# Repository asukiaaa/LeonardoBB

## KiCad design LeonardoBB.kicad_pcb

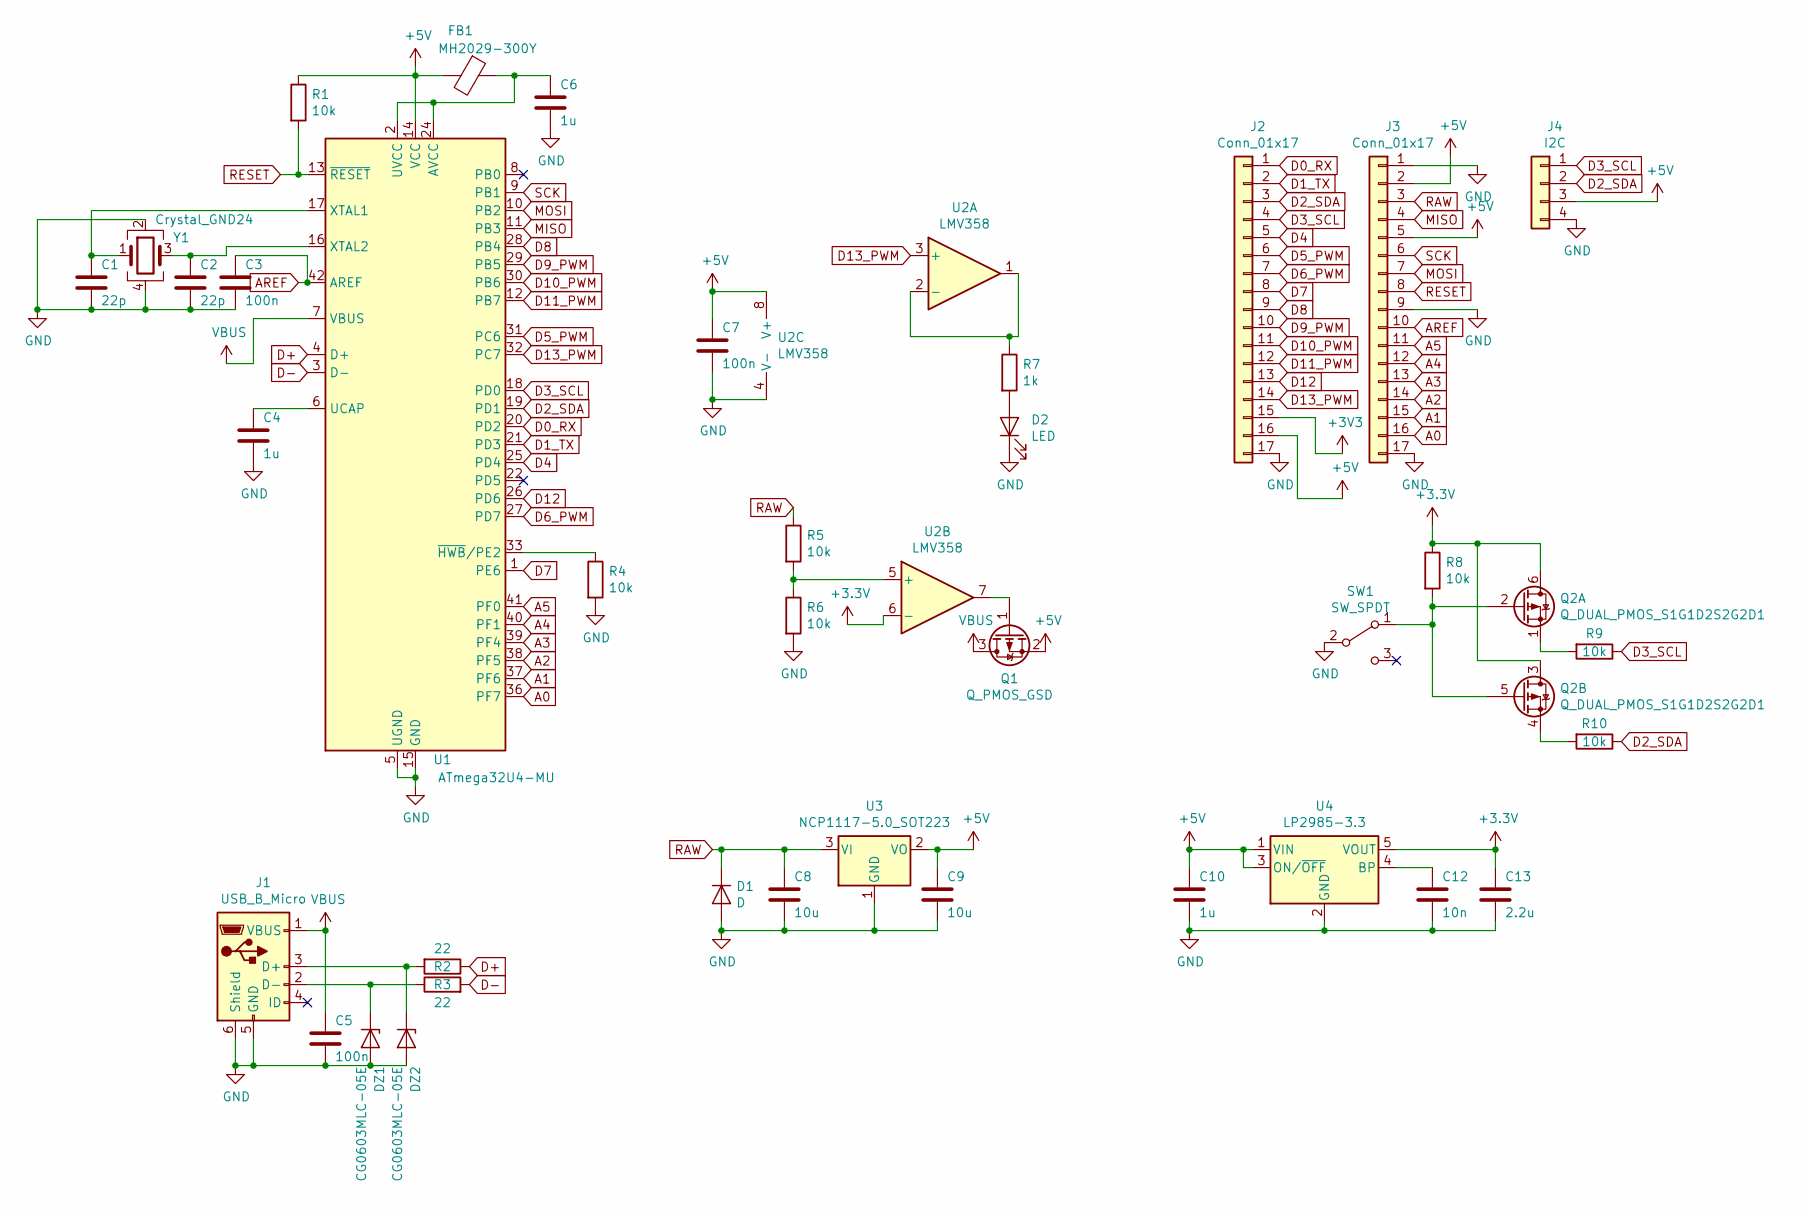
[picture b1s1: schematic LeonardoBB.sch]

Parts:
C1, C2: 22p; C_0402_1005Metric
C3, C5, C7: 100n; C_0402_1005Metric
C4, C6, C10: 1u; C_0402_1005Metric
C8, C9: 10u; C_0805_2012Metric
C12: 10n; C_0402_1005Metric
C13: 2.2u; C_0402_1005Metric
D1: D; D_SMA
D2: LED; LED_0603_1608Metric
DZ1, DZ2: CG0603MLC-05E; D_0603_1608Metric
FB1: MH2029-300Y; C_0805_2012Metric
J1: USB_B_Micro; USB_Micro-B_Molex-105017-0001
J2, J3: Conn_01x17; PinSocket_1x17_P2.54mm_Vertical_without_silk
J4: I2C; NS-Tech_Grove_1x04_P2mm_Vertical
Q1: Q_PMOS_GSD; SuperSOT-3
Q2: Q_DUAL_PMOS_S1G1D2S2G2D1; SOT-363_SC-70-6
R1, R4, R5, R6, R8, R9, R10: 10k; R_0603_1608Metric
R2, R3: 22; R_0603_1608Metric
R7: 1k; R_0603_1608Metric
SW1: SW_SPDT; SW_SPDT_PCM12
U1: ATmega32U4-MU; QFN-44-1EP_7x7mm_P0.5mm_EP5.2x5.2mm
U2: LMV358; VSSOP-8_3.0x3.0mm_P0.65mm
U3: NCP1117-5.0_SOT223; SOT-223-3_TabPin2
U4: LP2985-3.3; SOT-23-5
Y1: Crystal_GND24; Crystal_SMD_SeikoEpson_TSX3225-4Pin_3.2x2.5mm

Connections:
+5V: C7.1, C9.1, C10.1, FB1.2, J2.16, J3.2, J3.5, J4.3, Q1.2 (S), R1.1, U1.14 (VCC), U1.34 (VCC), U2.8 (V+), U3.2 (VO), U4.1 (VIN), U4.3 (ON/~OFF~)
A0: J3.16, U1.36 (PF7)
A1: J3.15, U1.37 (PF6)
A2: J3.14, U1.38 (PF5)
A3: J3.13, U1.39 (PF4)
A4: J3.12, U1.40 (PF1)
A5: J3.11, U1.41 (PF0)
AREF: C3.1, J3.10, U1.42 (AREF)
D0_RX: J2.1, U1.20 (PD2)
D1_TX: J2.2, U1.21 (PD3)
D2_SDA: J2.3, J4.2, R10.1, U1.19 (PD1)
D3_SCL: J2.4, J4.1, R9.1, U1.18 (PD0)
D4: J2.5, U1.25 (PD4)
D5_PWM: J2.6, U1.31 (PC6)
D6_PWM: J2.7, U1.27 (PD7)
D7: J2.8, U1.1 (PE6)
D8: J2.9, U1.28 (PB4)
D9_PWM: J2.10, U1.29 (PB5)
D10_PWM: J2.11, U1.30 (PB6)
D11_PWM: J2.12, U1.12 (PB7)
D12: J2.13, U1.26 (PD6)
D13_PWM: J2.14, U1.32 (PC7), U2.3 (+)
D+: R2.1, U1.4 (D+)
D-: R3.2, U1.3 (D-)
GND: C1.2, C2.2, C3.2, C4.2, C5.2, C6.2, C7.2, C8.2, C9.2, C10.2, C12.2, C13.2, D1.2 (A), D2.1 (K), DZ1.2 (A), DZ2.2 (A), J1.5 (GND), J1.6 (Shield), J2.17, J3.1, J3.9, J3.17, J4.4, R4.2, R6.2, SW1.2 (B), U1.5 (UGND), U1.15 (GND), U1.23 (GND), U1.35 (GND), U1.43 (GND), U1.45 (GND), U2.4 (V-), U3.1 (GND), U4.2 (GND), Y1.2, Y1.4
MISO: J3.4, U1.11 (PB3)
MOSI: J3.7, U1.10 (PB2)
unnamed: C1.1, U1.17 (XTAL1), Y1.1
unnamed: C2.1, U1.16 (XTAL2), Y1.3
unnamed: C4.1, U1.6 (UCAP)
unnamed: C6.1, FB1.1, U1.2 (UVCC), U1.24 (AVCC), U1.44 (AVCC)
unnamed: C12.1, U4.4 (BP)
unnamed: D2.2 (A), R7.2
unnamed: DZ1.1 (K), J1.2 (D-), R3.1
unnamed: DZ2.1 (K), J1.3 (D+), R2.2
unnamed: Q1.1 (G), U2.7
unnamed: Q2.1 (S), R9.2
unnamed: Q2.2 (G), Q2.5 (G), R8.2, SW1.1 (A)
unnamed: Q2.4 (S), R10.2
unnamed: R4.1, U1.33 (~HWB~/PE2)
unnamed: R5.2, R6.1, U2.5 (+)
unnamed: R7.1, U2.1, U2.2 (-)
RAW: C8.1, D1.1 (K), J3.3, R5.1, U3.3 (VI)
RESET: J3.8, R1.2, U1.13 (~RESET)
SCK: J3.6, U1.9 (PB1)
VBUS: C5.1, J1.1 (VBUS), Q1.3 (D), U1.7 (VBUS)

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
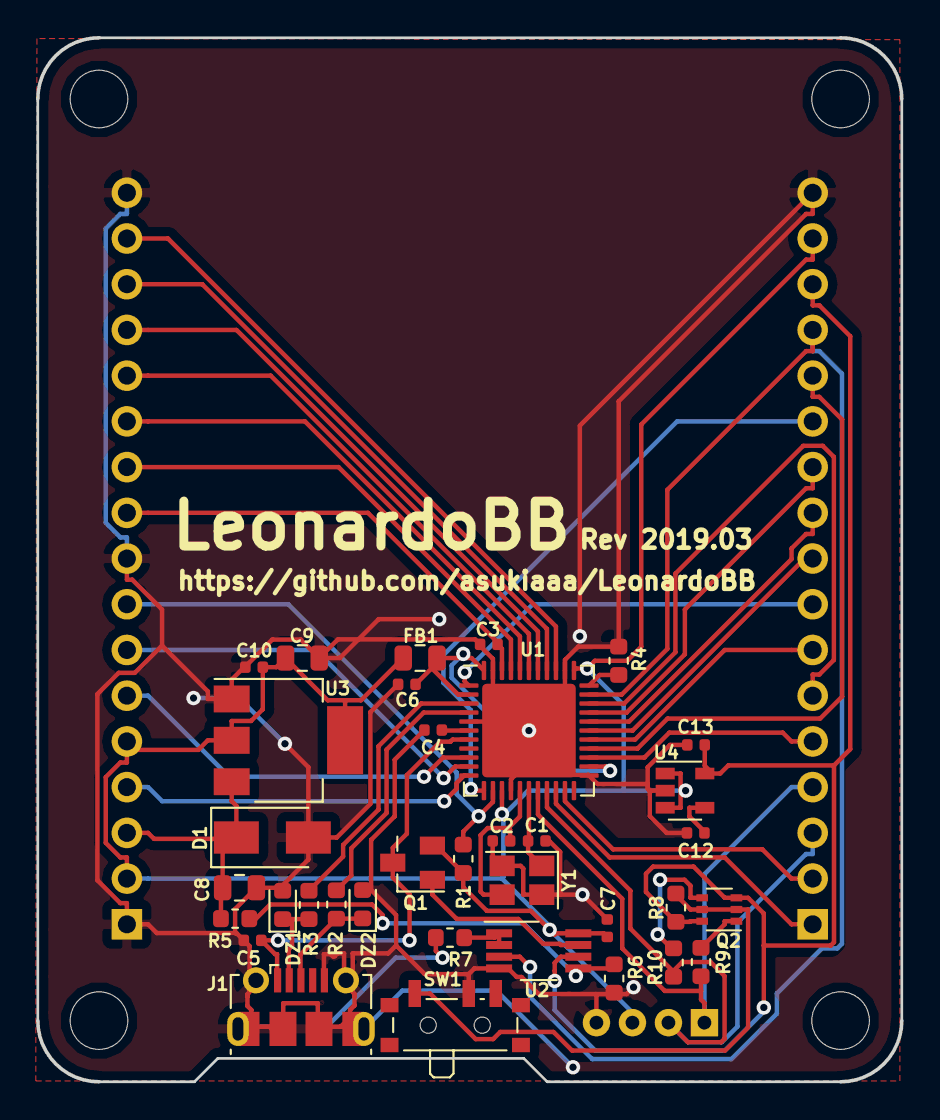
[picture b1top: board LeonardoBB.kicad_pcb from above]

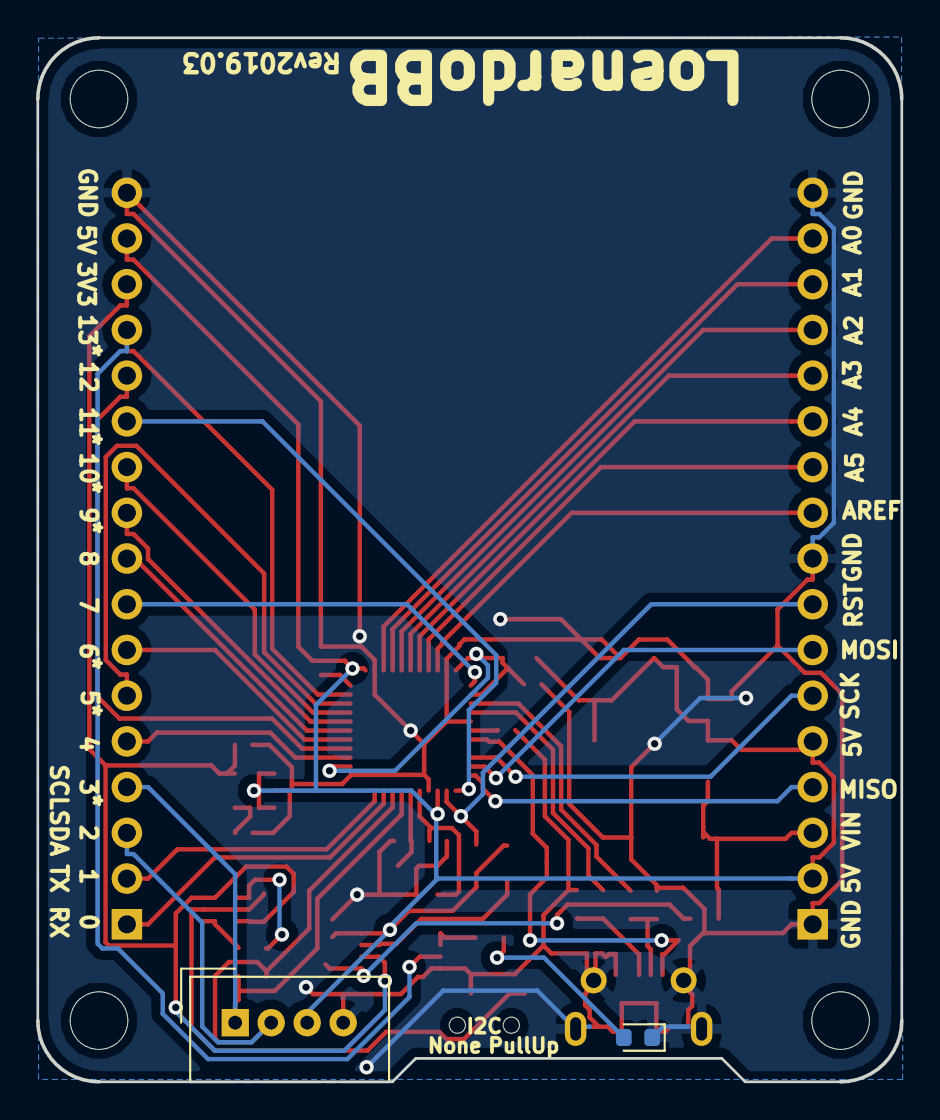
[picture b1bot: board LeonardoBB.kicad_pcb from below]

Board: 2 copper layers, 48.0 x 58.0 mm, 43 parts (4 on the bottom side), 47 nets.

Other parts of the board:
REF1, REF2, REF3, REF4: MountingHole_3.2mm_M3

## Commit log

2019-03-17 Change footprints for USB and LMV358
2019-03-17 Update gerber files to order for fusion PCB
2019-03-17 Add readme
2019-03-18 Add reset switch
